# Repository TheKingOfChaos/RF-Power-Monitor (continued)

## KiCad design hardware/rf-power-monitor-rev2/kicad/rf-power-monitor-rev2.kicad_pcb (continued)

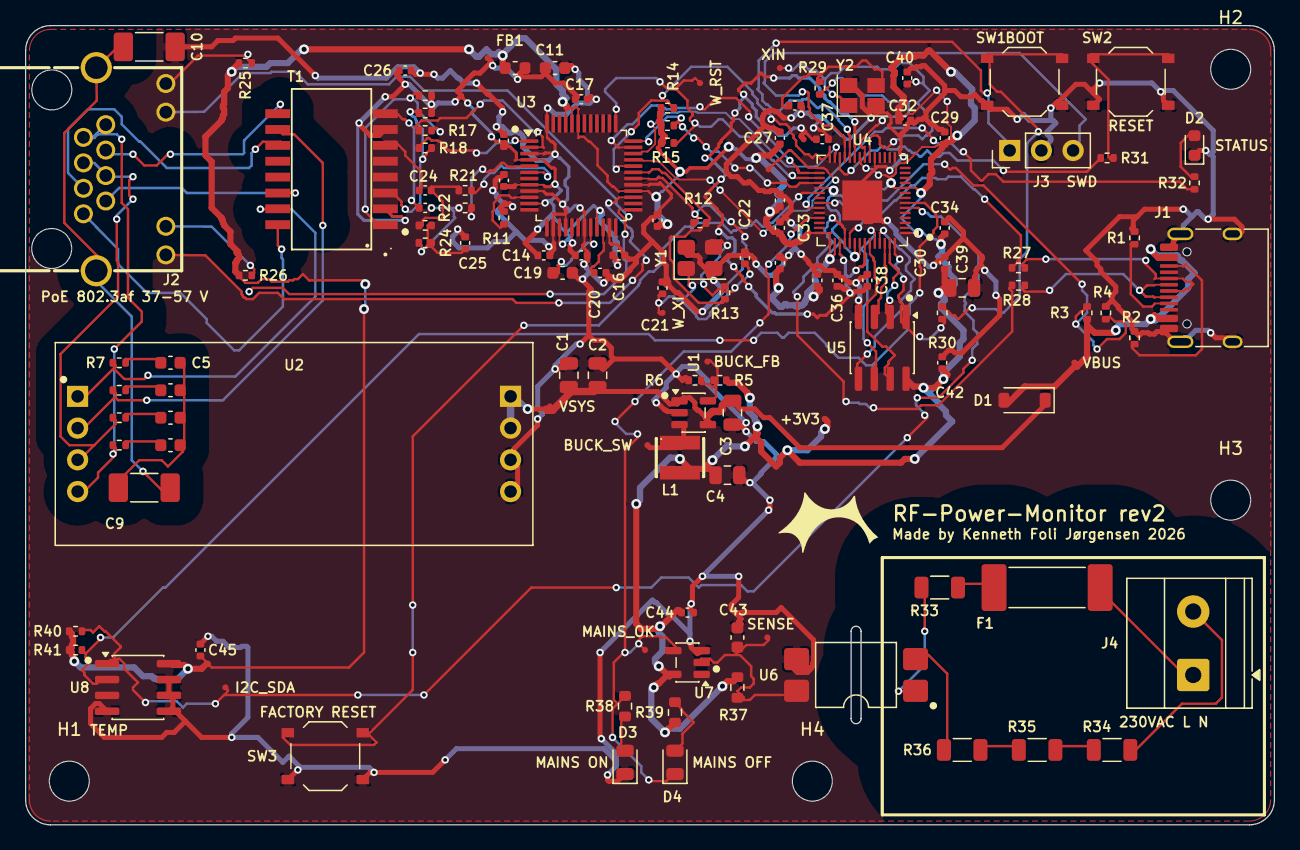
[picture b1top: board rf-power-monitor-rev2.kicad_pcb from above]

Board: 2 copper layers, 100.0 x 64.0 mm, 129 parts (0 on the bottom side), 86 nets.

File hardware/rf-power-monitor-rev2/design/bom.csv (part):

ref,value,function,mpn,manufacturer,package,source,lcsc,stock_checked_2026-11-02,mpn_url,note
J1,USB-C,power,TYPE-C-31-M-12,Korean Hroparts,USB_C_Receptacle_HRO_TYPE-C-31-M-12,LCSC,C165948,159060,https://www.lcsc.com/product-detail/C165948.html,"USB 2.0 device: serial menu, flashing, bench power"
R1,5.1k,power,0402WGF5101TCE,,R_0402_1005Metric,LCSC,C25905,1948800,https://www.lcsc.com/product-detail/C25905.html,UFP Rd
R2,5.1k,power,0402WGF5101TCE,,R_0402_1005Metric,LCSC,C25905,1948800,https://www.lcsc.com/product-detail/C25905.html,UFP Rd
D1,B5819W,power,B5819W SL,Slkor,D_SOD-123,LCSC,C8598,506320,https://www.lcsc.com/product-detail/C8598.html,VBUS to VSYS OR-ing: PoE 5 V never back-feeds USB
R3,5.6k,power,0402WGF5601TCE,,R_0402_1005Metric,LCSC,C25908,343200,https://www.lcsc.com/product-detail/C25908.html,VBUS sense to GP24 (as on the Pico)
R4,10k,power,RC0402FR-0710KL,,R_0402_1005Metric,LCSC,C60490,1426200,https://www.lcsc.com/product-detail/C60490.html,
C1,22uF,power,CL21A226MAQNNNE,,C_0805_2012Metric,LCSC,C45783,1837220,https://www.lcsc.com/product-detail/C45783.html,VSYS bulk
C2,22uF,power,CL21A226MAQNNNE,,C_0805_2012Metric,LCSC,C45783,1837220,https://www.lcsc.com/product-detail/C45783.html,VSYS bulk
U1,TLV62569DBVR,power,TLV62569DBVR,Texas Instruments,SOT-23-5,LCSC,C141836,273775,https://www.lcsc.com/product-detail/C141836.html,"2 A sync buck, 1.5 MHz: VSYS 4.4-5.25 V to 3V3"
C3,10uF,power,CL21A106KAYNNNE,,C_0805_2012Metric,LCSC,C15850,1186280,https://www.lcsc.com/product-detail/C15850.html,"buck input, at U1 pin 4"
L1,2.2uH,power,SWPA3015S2R2MT,Sunlord,IND-SMD_L3.0-W3.0,LCSC,C43389,43089,https://www.lcsc.com/product-detail/C43389.html,2.2 uH 2 A (TI table 4 standard LC)
C4,22uF,power,CL21A226MAQNNNE,,C_0805_2012Metric,LCSC,C45783,1837220,https://www.lcsc.com/product-detail/C45783.html,buck output (TI table 4: 10-47 uF)
R5,100k,power,0402WGF1003TCE,,R_0402_1005Metric,LCSC,C25741,1185400,https://www.lcsc.com/product-detail/C25741.html,FB top: 0.6 V x (1 + 100k/22k) = 3.327 V
R6,22k,power,RC0402FR-0722KL,,R_0402_1005Metric,LCSC,C82868,4250937,https://www.lcsc.com/product-detail/C82868.html,FB bottom
J2,RJ45,poe,KH-RJ45-56-8P8C-D,Kinghelm,RJ45-TH_KH-RJ45-56-8P8C-D,LCSC,C2828082,5700,https://www.lcsc.com/product-detail/C2828082.html,"shielded, LEDs, no magnetics; MDI (W5500 has no auto-MDIX)"
T1,HR601680,poe,HR601680,HanRun,SMD-16_L12.7-W7.2-P1.27-LS9.5-BL,LCSC,C242560,15162,https://www.lcsc.com/product-detail/C242560.html,"10/100 1CT:1CT 350 uH, 1500 Vrms; line CTs carry PoE (about 30 mA here)"
R7,75R,poe,RC0402FR-0775RL,,R_0402_1005Metric,LCSC,C114757,209600,https://www.lcsc.com/product-detail/C114757.html,
R8,75R,poe,RC0402FR-0775RL,,R_0402_1005Metric,LCSC,C114757,209600,https://www.lcsc.com/product-detail/C114757.html,
R9,75R,poe,RC0402FR-0775RL,,R_0402_1005Metric,LCSC,C114757,209600,https://www.lcsc.com/product-detail/C114757.html,
R10,75R,poe,RC0402FR-0775RL,,R_0402_1005Metric,LCSC,C114757,209600,https://www.lcsc.com/product-detail/C114757.html,
C5,10nF 100V,poe,CC0603KRX7R0BB103,,C_0603_1608Metric,LCSC,C107059,755900,https://www.lcsc.com/product-detail/C107059.html,
C6,10nF 100V,poe,CC0603KRX7R0BB103,,C_0603_1608Metric,LCSC,C107059,755900,https://www.lcsc.com/product-detail/C107059.html,
C7,10nF 100V,poe,CC0603KRX7R0BB103,,C_0603_1608Metric,LCSC,C107059,755900,https://www.lcsc.com/product-detail/C107059.html,
C8,10nF 100V,poe,CC0603KRX7R0BB103,,C_0603_1608Metric,LCSC,C107059,755900,https://www.lcsc.com/product-detail/C107059.html,
C9,1nF 2kV,poe,1808B102K202NT,,C_1808_4520Metric,LCSC,C81332,20170,https://www.lcsc.com/product-detail/C81332.html,Bob Smith to chassis
C10,1nF 2kV,poe,1808B102K202NT,,C_1808_4520Metric,LCSC,C81332,20170,https://www.lcsc.com/product-detail/C81332.html,chassis to logic GND (as WIZnet C3)
U3,W5500,eth,W5500,WIZnet,LQFP-48_7x7mm_P0.5mm,LCSC,C32843,18523,https://www.lcsc.com/product-detail/C32843.html,"PMODE 111: all capable, auto-negotiation"
FB1,120R@100MHz,eth,GZ1608D121TF,Sunlord,L_0603_1608Metric,LCSC,C12391,149712,https://www.lcsc.com/product-detail/C12391.html,3V3 to W5500 analog supply
C11,4.7uF,eth,CL10A475KO8NNNC,,C_0603_1608Metric,LCSC,C19666,1134420,https://www.lcsc.com/product-detail/C19666.html,AVDD bulk
C12,100nF,eth,CL05B104KO5NNNC,,C_0402_1005Metric,LCSC,C1525,20188300,https://www.lcsc.com/product-detail/C1525.html,"AVDD, one per pin 4/8/11/15/17/21"
C13,100nF,eth,CL05B104KO5NNNC,,C_0402_1005Metric,LCSC,C1525,20188300,https://www.lcsc.com/product-detail/C1525.html,"AVDD, one per pin 4/8/11/15/17/21"
C14,100nF,eth,CL05B104KO5NNNC,,C_0402_1005Metric,LCSC,C1525,20188300,https://www.lcsc.com/product-detail/C1525.html,"AVDD, one per pin 4/8/11/15/17/21"
C15,100nF,eth,CL05B104KO5NNNC,,C_0402_1005Metric,LCSC,C1525,20188300,https://www.lcsc.com/product-detail/C1525.html,"AVDD, one per pin 4/8/11/15/17/21"
C16,100nF,eth,CL05B104KO5NNNC,,C_0402_1005Metric,LCSC,C1525,20188300,https://www.lcsc.com/product-detail/C1525.html,"AVDD, one per pin 4/8/11/15/17/21"
C17,100nF,eth,CL05B104KO5NNNC,,C_0402_1005Metric,LCSC,C1525,20188300,https://www.lcsc.com/product-detail/C1525.html,"AVDD, one per pin 4/8/11/15/17/21"
C18,100nF,eth,CL05B104KO5NNNC,,C_0402_1005Metric,LCSC,C1525,20188300,https://www.lcsc.com/product-detail/C1525.html,VDD pin 28
C19,4.7uF,eth,CL10A475KO8NNNC,,C_0603_1608Metric,LCSC,C19666,1134420,https://www.lcsc.com/product-detail/C19666.html,"TOCAP: datasheet 4.7 uF, short trace"
C20,10nF,eth,CL05B103KB5NNNC,,C_0402_1005Metric,LCSC,C15195,1800000,https://www.lcsc.com/product-detail/C15195.html,1V2O: datasheet 10 nF
R11,12.4k 1%,eth,0402WGF1242TCE,,R_0402_1005Metric,LCSC,C11692,346100,https://www.lcsc.com/product-detail/C11692.html,"EXRES1 to AGND, datasheet"
Y1,25MHz,eth,X322525MOB4SI,YXC,Crystal_SMD_3225-4Pin_3.2x2.5mm,LCSC,C9006,226845,https://www.lcsc.com/product-detail/C9006.html,"CL 12 pF, +-10 ppm: 2 x 18 pF + ~3 pF stray"
R12,1M,eth,0402WGF1004TCE,,R_0402_1005Metric,LCSC,C26083,1018000,https://www.lcsc.com/product-detail/C26083.html,crystal bias (WIZnet R24)
R13,0R,eth,0402WGF0000TCE,,R_0402_1005Metric,LCSC,C17168,2363600,https://www.lcsc.com/product-detail/C17168.html,drive-level option (WIZnet R23)
C21,18pF,eth,0402CG180J500NT,,C_0402_1005Metric,LCSC,C1549,796300,https://www.lcsc.com/product-detail/C1549.html,
C22,18pF,eth,0402CG180J500NT,,C_0402_1005Metric,LCSC,C1549,796300,https://www.lcsc.com/product-detail/C1549.html,
R14,4.7k,eth,0402WGF4701TCE,,R_0402_1005Metric,LCSC,C25900,7063400,https://www.lcsc.com/product-detail/C25900.html,SCSn idle high while RP2040 boots
R15,4.7k,eth,0402WGF4701TCE,,R_0402_1005Metric,LCSC,C25900,7063400,https://www.lcsc.com/product-detail/C25900.html,
R16,4.7k,eth,0402WGF4701TCE,,R_0402_1005Metric,LCSC,C25900,7063400,https://www.lcsc.com/product-detail/C25900.html,
R17,3.3R,eth,RC0402FR-073R3L,,R_0402_1005Metric,LCSC,C137986,3410,https://www.lcsc.com/product-detail/C137986.html,
R18,3.3R,eth,RC0402FR-073R3L,,R_0402_1005Metric,LCSC,C137986,3410,https://www.lcsc.com/product-detail/C137986.html,
R19,49.9R,eth,0402WGF499JTCE,,R_0402_1005Metric,LCSC,C25120,338300,https://www.lcsc.com/product-detail/C25120.html,
R20,49.9R,eth,0402WGF499JTCE,,R_0402_1005Metric,LCSC,C25120,338300,https://www.lcsc.com/product-detail/C25120.html,
C23,6.8nF,eth,0402B682K500NT,,C_0402_1005Metric,LCSC,C1542,64600,https://www.lcsc.com/product-detail/C1542.html,
C24,6.8nF,eth,0402B682K500NT,,C_0402_1005Metric,LCSC,C1542,64600,https://www.lcsc.com/product-detail/C1542.html,
R21,3.3R,eth,RC0402FR-073R3L,,R_0402_1005Metric,LCSC,C137986,3410,https://www.lcsc.com/product-detail/C137986.html,
R22,3.3R,eth,RC0402FR-073R3L,,R_0402_1005Metric,LCSC,C137986,3410,https://www.lcsc.com/product-detail/C137986.html,
R23,49.9R,eth,0402WGF499JTCE,,R_0402_1005Metric,LCSC,C25120,338300,https://www.lcsc.com/product-detail/C25120.html,
R24,49.9R,eth,0402WGF499JTCE,,R_0402_1005Metric,LCSC,C25120,338300,https://www.lcsc.com/product-detail/C25120.html,
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
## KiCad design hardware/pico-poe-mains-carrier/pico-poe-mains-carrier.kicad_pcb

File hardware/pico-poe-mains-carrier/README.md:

# W5500-EVB-Pico-PoE mains monitor carrier

A 2-layer carrier board for the WIZnet W5500-EVB-Pico-PoE. It is 80 x 51.5 mm: exactly as long as the module, so both short edges line up with the module. The board extends 1.5 mm above the module for the solder fillets. It has 5x M3 holes, with centres at (4, 25.5), (4, 46) and (76, 46) mm from the module's top-left corner, plus H4 (30, 10.5) and H5 (66.5, 10.5) under the module, between the header rows.
All SMD parts are on the top side. The only through-hole parts are the module headers and the screw terminal.

The successor, [rev 2](../rf-power-monitor-rev2/README.md), puts the RP2040 and W5500 on one board with these circuits (designed, not built yet).

## What it does

| Function | Connection |
|---|---|
| 230 VAC present / absent | **GP27** (module pin 32): HIGH = mains present, LOW = mains absent |
| LED indication (hardware, no firmware needed) | Green D1 = mains ON, red D2 = mains OFF |
| Temperature | TMP1075 on I2C0: **GP4 = SDA, GP5 = SCL**, address **0x48** |
| Factory reset | SW1 from **GP22** (module pin 29) to GND, below the module; hold 10 s (the firmware's internal pull-up holds GP22 high) |
| Power | From the module's 3V3(OUT) pin 36 (the module is PoE powered) |

GP16 to GP21 are used by the on-board W5500 and are not used here.

## Mounting the module

| Soldered flat | On female headers |
|---|---|
|  |  |
|  |  |

You can mount the module in either of two ways; the footprint supports both.

- **Socketed:** two 1x20 female headers (2.54 mm, 8.5 mm high, e.g. LCSC C2905423) in the through-hole pads, and two 1x20 male headers (2.5 mm body) soldered under the module. The module sits 11 mm above the carrier and stays removable. Use all five mounting holes: screw the carrier down through H4 and H5 first (a normal M3 pan or cheese head fits easily), then plug the module in.
- **Soldered flat:** the module's long edges are castellated, and every pin has a pad that reaches 1 mm past the module edge. Solder the castellations directly; no headers are needed. H4 and H5 are covered by the module and stay empty; mount the carrier by H1 to H3.

For flat mounting, the carrier has clearance for the parts that stick out under the module. The positions come from WIZnet's V1.1 drill file.
- A corner notch for the RJ45 pins, posts and shield tabs, and for the PoE module's first 1x4 header (x 20.4 mm).
- A window for the PoE module's second 1x4 header (x 55.0 mm) and the SWD header (x 58.5 mm).
- A notch at the USB end for the USB-C shell and its tabs, which reach 0.37 mm below the module.

Trim any header pins under the module flush before soldering it down.

## Circuit

- 230 VAC goes in on J1 (L/N, 5.08 mm screw terminal on the right edge; the wires enter from the same end as the USB port).
- F1 (SETfuse SCT1032T1A250V, T 1 A, 250 VAC, 100 A breaking capacity) follows J1 in L. The mains side is a single series loop (L, F1, R1, optocoupler, R4, R3, R2, N), so F1 carries any fault current on the board, whichever way L and N are wired. The loop carries only about 1.2 mA and a single shorted resistor still leaves at least 204 k, so F1 is there for hard faults (an arc-over, L and N bridged), which a T 1 A fuse clears as well as a smaller one. It does not replace the upstream fuse.
- Four 68 k 1206 resistors rated 200 V (R1 in L, R2 to R4 in N) limit the current to about 1.2 mA peak, about 50 mW per resistor.
- An LTV-814S AC-input optocoupler (5 kVrms) pulls SENSE low on both half-cycles.
- C1 (1 µF) with R5 (47 k) bridges the zero crossings, so SENSE goes high about 30 to 50 ms after mains is lost.
- A 74LVC1G14 Schmitt inverter produces a clean MAINS_OK signal. It drives GP27 and both LEDs.

## Isolation

The mains area is on the right, below the module's USB end, outlined on silkscreen ("DANGER 230VAC"). The low-voltage logic, LEDs and temperature sensor are on the left. MAINS_OK, +3V3 and I2C reach them on the bottom layer, running between the module's two header rows.

- Mains copper is at least 6.5 mm from everything else, with at least 6.4 mm creepage. Both are enforced as DRC rules in `pico-poe-mains-carrier.kicad_dru`.
- A routed slot under the optocoupler lengthens the creepage path.
- There is no copper pour and there are no vias inside the mains area.
- The mounting holes are well away from the mains area.

## Files

- `pico-poe-mains-carrier.kicad_pro/.kicad_sch/.kicad_pcb`: the KiCad 10 project
- `PicoPoE_Carrier.kicad_sym`, `PicoPoE_Carrier.pretty/`: project symbols and the module footprint
- `fab/`: Gerbers and drill (zip), BOM and CPL in JLCPCB format, schematic PDF, STEP model
- `tools/generate.py`: generates the whole project; `tools/check.sh` runs ERC and DRC; `tools/fab.sh` exports the fab files

## Assembly notes

- Socketed: fit 2x 1x20 female headers (not in the BOM). Flat: solder the castellated edges, no headers needed.
- The module (U1) is excluded from the BOM and CPL.
- F1 is LCSC C19712559 (SETfuse SCT1032, 10.3 x 3.3 mm) on the Schurter UMT 250 footprint (10.1 x 3.1 mm); check it in JLCPCB's placement preview. A Schurter 3403.0156.11 (T 100 mA) fits the same pads. SW1 is LCSC C318884.
- Check the rotation of U2, U3 and U4 in JLCPCB's placement preview before ordering.
- The temperature reading includes some self-heating from the board and module. For true ambient, mount the board vertically or add an offset in firmware.
- Mains wiring must be done by a qualified person. The board must sit in a closed enclosure, and the supply must be fused upstream.

## Firmware

The firmware in this repository (C++, see the [main README](../../README.md)) runs on the module unchanged: it reads MAINS_OK on GP27 (HIGH = mains present) and uses the on-board W5500 on GP16-GP21. It reads the TMP1075 every 2 s as `ambientTemperature` (SNMP 63050.5, status screen, web page). Its 10 s factory reset reads SW1 on GP22 (active low).

## Firmware sketch (MicroPython)

```python
from machine import Pin, I2C
mains = Pin(27, Pin.IN)
i2c = I2C(0, sda=Pin(4), scl=Pin(5), freq=400_000)
raw = i2c.readfrom_mem(0x48, 0x00, 2)
temp_c = ((raw[0] << 8 | raw[1]) >> 4) * 0.0625   # sign-extend for < 0 C
print("mains", "ON" if mains.value() else "OFF", "temp", temp_c)
```

## Repository layout

```
pico-poe-mains-carrier/
├── pico-poe-mains-carrier.kicad_pro   KiCad 10 project
├── pico-poe-mains-carrier.kicad_sch   schematic
├── pico-poe-mains-carrier.kicad_pcb   PCB
├── pico-poe-mains-carrier.kicad_dru   custom design rules (230 VAC isolation)
├── PicoPoE_Carrier.kicad_sym          project symbol library
├── PicoPoE_Carrier.pretty/            project footprint library (module footprint)
├── sym-lib-table, fp-lib-table        project library tables (paths are relative)
├── fab/                               Gerbers, BOM, CPL, schematic PDF (see fab/README.md)
├── images/                            renders: top, bottom, 3D and side views; module soldered flat
│                                      (iso, side-flat), on headers (*-headers) and carrier only
├── 3d/                                STEP + GLB of the board with the module soldered flat and on
│                                      headers, STEP of the carrier only, and WIZnet's module model
└── tools/
    ├── generate.py                    generates the whole KiCad project
    ├── check.sh                       regenerate + ERC + DRC (needs kicad-cli 10)
    ├── fab.sh                         export the files in fab/
    ├── render.sh                      render images/ and export 3d/
    └── stock_fp/                      copies of the KiCad 10 library footprints used
```

All library paths are relative (`${KIPRJMOD}`), so the folder works anywhere. For example, you can place it at `hardware/pico-poe-mains-carrier/` in your firmware repository. Stock footprints and 3D models come from the standard KiCad 10 libraries.

`tools/generate.py` rewrites the schematic and PCB. If you edit the board by hand in KiCad, either copy the change into `generate.py` or stop using the generator; otherwise your edit will be overwritten.

`3d/W5500-EVB-Pico-PoE_V1.1.step` is WIZnet's 3D model of the module, from https://docs.wiznet.io/Product/Chip/Ethernet/W5500/W5500-EVB-Pico-PoE. The module footprint shows it soldered flat. The cutouts in the carrier match WIZnet's V1.1 drill file.

The footprints in `tools/stock_fp/` are from the KiCad library, licensed CC-BY-SA 4.0 with an exception for designs made with them (https://www.kicad.org/libraries/license/).

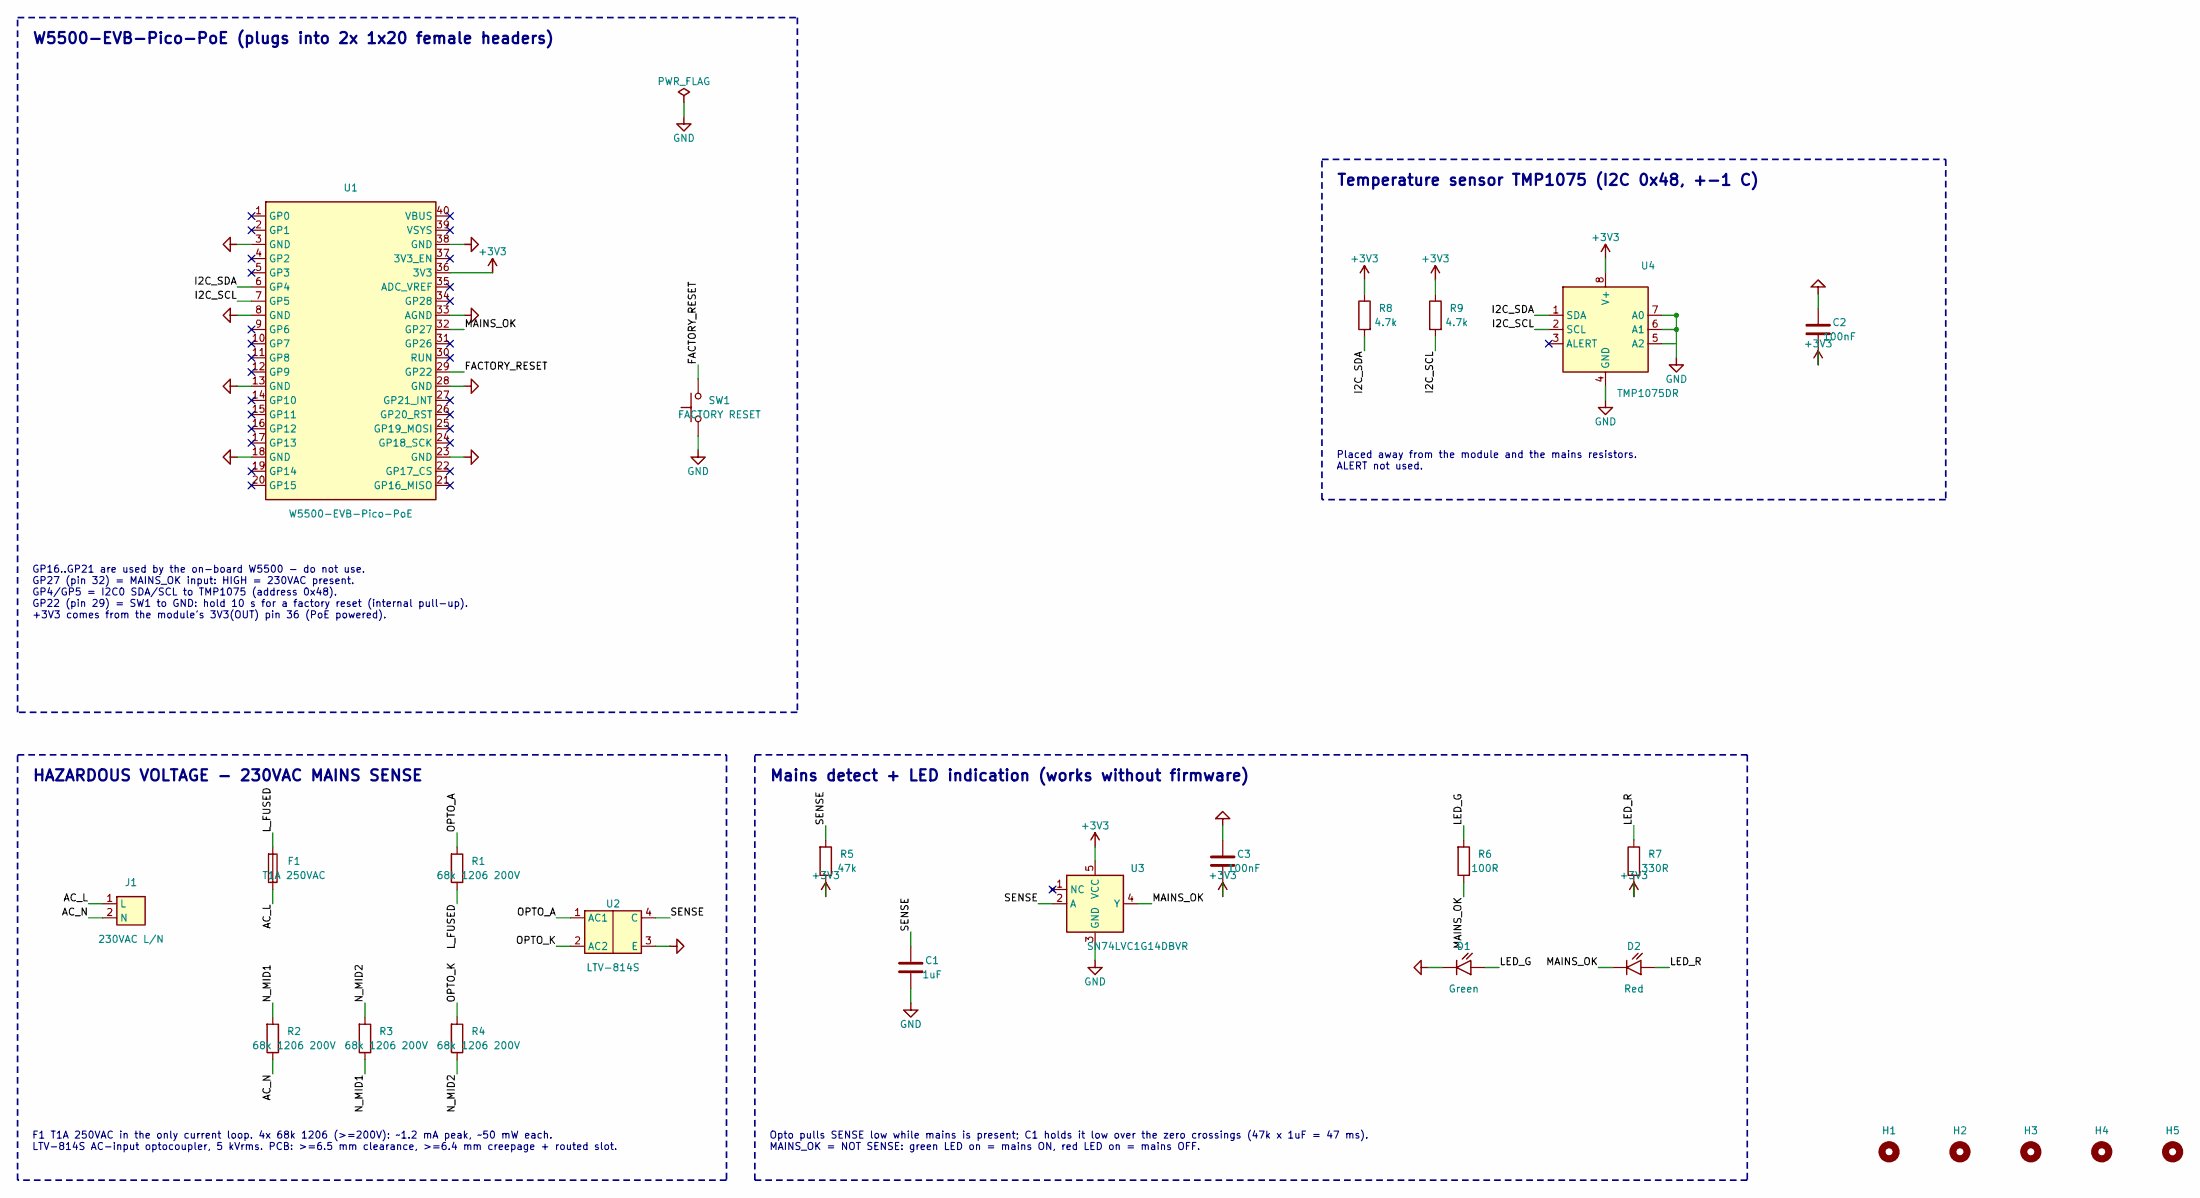
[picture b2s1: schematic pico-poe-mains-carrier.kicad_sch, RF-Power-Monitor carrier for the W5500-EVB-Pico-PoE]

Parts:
C1: 1uF; C_0603_1608Metric; LCSC C15849
C2, C3: 100nF; C_0603_1608Metric; LCSC C14663
D1: Green; LED_0805_2012Metric; LCSC C2297
D2: Red; LED_0805_2012Metric; LCSC C84256
F1: T1A 250VAC; Fuse_Schurter_UMT250; MPN SETfuse SCT1032T1A250V (T 1 A, 250 VAC,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; LCSC C19712559
H1, H2, H3: MountingHole_3.2mm_M3
H4, H5: MountingHole_3.2mm_M3; MountingHole_3.2mm_M3_UnderModule
J1: 230VAC L/N; TerminalBlock_Phoenix_MKDS-1,5-2-5.08_1x02_P5.08mm_Horizont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; MPN Phoenix 1715721 (MKDS 1,5/2-5,08)
R1, R2, R3, R4: 68k 1206 200V; R_1206_3216Metric; LCSC C2889820
R5: 47k; R_0603_1608Metric; LCSC C25819
R6: 100R; R_0603_1608Metric; LCSC C22775
R7: 330R; R_0603_1608Metric; LCSC C23138
R8, R9: 4.7k; R_0603_1608Metric; LCSC C23162
SW1: FACTORY RESET; SW_Push_1P1T_XKB_TS-1187A; MPN XKB TS-1187A-B-A-B; LCSC C318884
U1: W5500-EVB-Pico-PoE; W5500-EVB-Pico-PoE_Socket; MPN W5500-EVB-Pico-PoE
U2: LTV-814S; SMDIP-4_W9.53mm; MPN LTV-814S-TA1; LCSC C125118
U3: SN74LVC1G14DBVR; SOT-23-5; LCSC C7835
U4: TMP1075DR; SOIC-8_3.9x4.9mm_P1.27mm; LCSC C2878381

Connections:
+3V3: C2.1, C3.2, R5.2, R7.1, R8.2, R9.2, U1.36 (3V3), U3.5 (VCC), U4.8 (V+)
/AC_L: F1.2, J1.1 (L)
/AC_N: J1.2 (N), R2.2
/FACTORY_RESET: SW1.1, U1.29 (GP22)
/I2C_SCL: R9.1, U1.7 (GP5), U4.2 (SCL)
/I2C_SDA: R8.1, U1.6 (GP4), U4.1 (SDA)
/LED_G: D1.2 (A), R6.1
/LED_R: D2.2 (A), R7.2
/L_FUSED: F1.1, R1.2
/MAINS_OK: D2.1 (K), R6.2, U1.32 (GP27), U3.4 (Y)
/N_MID1: R2.1, R3.2
/N_MID2: R3.1, R4.2
/OPTO_A: R1.1, U2.1 (AC1)
/OPTO_K: R4.1, U2.2 (AC2)
/SENSE: C1.1, R5.1, U2.4 (C), U3.2 (A)
GND: C1.2, C2.2, C3.1, D1.1 (K), SW1.2, U1.3 (GND), U1.8 (GND), U1.13 (GND), U1.18 (GND), U1.23 (GND), U1.28 (GND), U1.33 (AGND), U1.38 (GND), U2.3 (E), U3.3 (GND), U4.4 (GND), U4.5 (A2), U4.6 (A1), U4.7 (A0)

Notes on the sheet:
W5500-EVB-Pico-PoE (plugs into 2x 1x20 female headers)
GP16..GP21 are used by the on-board W5500 - do not use. GP27 (pin 32) = MAINS_OK input: HIGH = 230VAC present. GP4/GP5 = I2C0 SDA/SCL to TMP1075 (address 0x48). GP22 (pin 29) = SW1 to GND: hold 10 s for a factory reset (internal pull-up). +3V3 comes from the module's 3V3(OUT) pin 36 (PoE powered).
HAZARDOUS VOLTAGE - 230VAC MAINS SENSE
F1 T1A 250VAC in the only current loop. 4x 68k 1206 (>=200V): ~1.2 mA peak, ~50 mW each. LTV-814S AC-input optocoupler, 5 kVrms. PCB: >=6.5 mm clearance, >=6.4 mm creepage + routed slot.
Mains detect + LED indication (works without firmware)
Opto pulls SENSE low while mains is present; C1 holds it low over the zero crossings (47k x 1uF = 47 ms). MAINS_OK = NOT SENSE: green LED on = mains ON, red LED on = mains OFF.
Temperature sensor TMP1075 (I2C 0x48, +-1 C)
Placed away from the module and the mains resistors. ALERT not used.

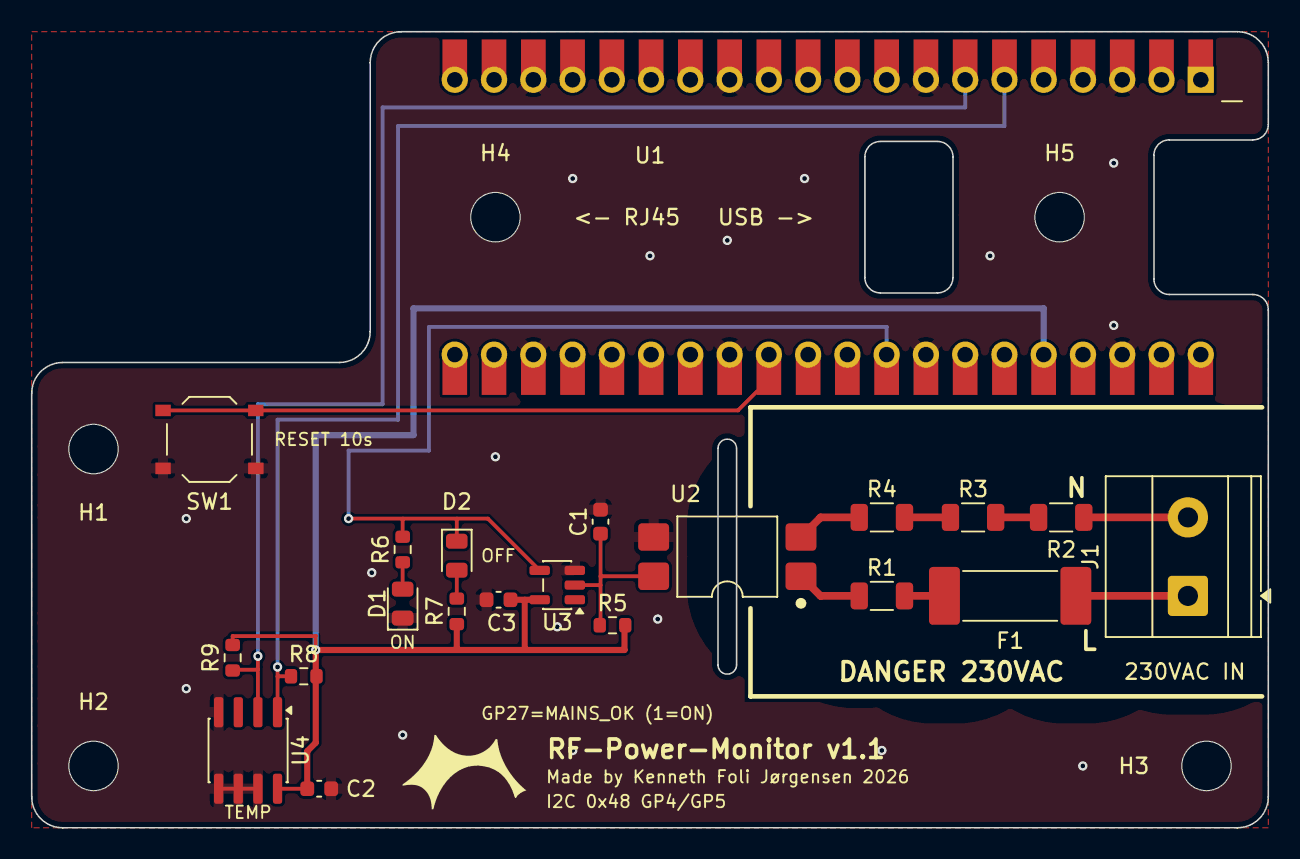
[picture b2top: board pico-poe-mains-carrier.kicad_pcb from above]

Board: 2 copper layers, 80.0 x 51.5 mm, 26 parts (0 on the bottom side), 16 nets.

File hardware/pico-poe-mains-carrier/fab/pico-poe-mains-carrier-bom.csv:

"Designator","Comment","Footprint","LCSC Part #","MPN","Quantity"
"C1","1uF","Capacitor_SMD:C_0603_1608Metric","C15849","","1"
"C2,C3","100nF","Capacitor_SMD:C_0603_1608Metric","C14663","","2"
"D1","Green","LED_SMD:LED_0805_2012Metric","C2297","","1"
"D2","Red","LED_SMD:LED_0805_2012Metric","C84256","","1"
"F1","T1A 250VAC","Fuse:Fuse_Schurter_UMT250","C19712559","SETfuse SCT1032T1A250V (T 1 A, 250 VAC, 100 A breaking)","1"
"J1","230VAC L/N","TerminalBlock_Phoenix:TerminalBlock_Phoenix_MKDS-1,5-2-5.08_1x02_P5.08mm_Horizontal","","Phoenix 1715721 (MKDS 1,5/2-5,08)","1"
"R1,R2,R3,R4","68k 1206 200V","Resistor_SMD:R_1206_3216Metric","C2889820","","4"
"R5","47k","Resistor_SMD:R_0603_1608Metric","C25819","","1"
"R6","100R","Resistor_SMD:R_0603_1608Metric","C22775","","1"
"R7","330R","Resistor_SMD:R_0603_1608Metric","C23138","","1"
"R8,R9","4.7k","Resistor_SMD:R_0603_1608Metric","C23162","","2"
"SW1","FACTORY RESET","Button_Switch_SMD:SW_Push_1P1T_XKB_TS-1187A","C318884","XKB TS-1187A-B-A-B","1"
"U2","LTV-814S","Package_DIP:SMDIP-4_W9.53mm","C125118","LTV-814S-TA1","1"
"U3","SN74LVC1G14DBVR","Package_TO_SOT_SMD:SOT-23-5","C7835","","1"
"U4","TMP1075DR","Package_SO:SOIC-8_3.9x4.9mm_P1.27mm","C2878381","","1"
